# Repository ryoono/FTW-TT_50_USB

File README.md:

# FTW-TT_50_USB  

<span style="color: red; ">F</span>ake <span style="color: red; ">T</span>ype <span style="color: red; ">W</span>riter - <span style="color: red; ">T</span>etora <span style="color: red; ">T</span>ech lab _ <span style="color: red; ">5</span>.<span style="color: red; ">0</span>v _ <span style="color: red; ">USB</span> drive  
テトラ技研製 USB駆動 ニセタイプライター  

**[紹介動画](https://youtu.be/UQrdH8_pX44?si=VVSs2FK_6RHxstvM)**

## 背景  
現代の消音キーボードに反抗すべく、タイプライターを叩いた時の音を楽しめるデバイスを作成する。  
タイプライター風キーボードも売ってはいるが、それを使っては味気ないので、外付けUSBデバイスとして実装する。  
当初、リレーで音を出そうと考えていたが、よくよく調べてみると二番煎じだった。  
そのため、急遽ソレノイドで音を出す仕様に変更した...   
[Silriumさん_USB KeyBoard RELAY](https://makezine.jp/blog/2015/08/mft2015_silrium.html)

## 概要  
キータイプ時にソレノイドを動作させ、タイプライターの音を表現する。  
音は2種類用意する。

| キー種類     | 音           | 備考                   | 
| ------------ | ------------ | ---------------------- | 
| 一般キー     | メカニカル音 | エンターキー以外のキー | 
| エンターキー | ベル音       |                        |  

メカニカル音はソレノイドの動作音で再現する。  
ベル音はタイプライターの文字送り催促ベルを指しており、自転車のベルで再現する。  

## ハードウェア設計  
### 構成  
一般キー押下時の音を再現するために、ソレノイドを接続する。  
タイピングの間隔が80msを下回ると、ソレノイドのデッドタイムとかぶるため、一般キー用のソレノイドを2つ接続して対策する。  
エンターキー押下時の音は、ベルを鳴らすことで対応する。  
なお、エンターキーの押下間隔は80msを下回らないと仮定して、ソレノイドは1つのみ接続する。  

### 回路図  
小型化を狙いpicマイコンで実装しようとしたが、時間が無いのでArduinoを使用する。  
Arduino Microを使用して設計したが、電源回りが弱いようで5Vピンから5V出力されないため、Nanoを使用する。  
使用するソレノイドには、ON/OFF 40[ms]ずつ計80[ms]のデッドタイムがあり、一般キー押下タイミングによっては、反応が追い付かない。  
そのため、ソレノイドを2個設置し、40[ms]のデッドタイムとすることで対応する。  
なお、2個以上のソレノイドを同時に動作させることはUSB2.0の規格上、電流が大きすぎるため同時動作ソレノイドは1つまでとする。  

## ソフトウェア設計  
### PC側  
```mermaid
---
title: Fig. PC側処理_フローチャート
---

flowchart TD
    start1([開始])
    node0[Arduinoとの通信開始]
    node1[キーイベント監視開始]
    end1([終了])

    start2([キーイベント発生])
    node2[押下キー取得]
    switch1{押下キー}
    node3[Arduinoに'0'を送信]
    node4[Arduinoに'1'を送信]
    end2([終了])

    start1 --> node0
    node0 --> node1
    node1 --> end1

    start2 --> node2
    node2 --> switch1
    switch1 -- エンターキー --> node3
    switch1 -- エンターキー以外 --> node4
    node3 --> end2
    node4 --> end2
```

### デバイス側  
なぜ関数化しなかったのかが悔やまれるが、展示ギリギリだったので許してほしい。  

```mermaid
---
title: Fig. Arduino側処理_フローチャート
---

flowchart TD
    start1([開始])
    node0[シリアル受信チェック]
    switch0{受信有無}
    switch1{打鍵タイプ}
    switch2{受信キー}
    switch2_1{受信キー}
    node1[受信キーBuff = エンターキー]
    switch3{受信キーBuff}
    node2[受信キーBuff = 一般キー]
    node2_1[受信キーBuff = 一般キー]
    switch4{ソレノイド状態}
    end1([終了])

    start1 --> node0
    node0 --> switch0
    switch0 -- あり --> switch1
    switch1 -- 英語(1) --> switch2
    switch2 -- エンターキー('0') --> node1
    switch2 -- 一般キー('1') --> switch3
    switch3 -- なし(0) --> node2
    switch1 -- 日本語(0) --> switch2_1
    switch2_1 -- エンターキー('0') | 一般キー('1') --> node2_1
    node1 --> switch4
    node2 --> switch4
    switch2 -- それ以外--> switch4
    switch3 -- あり(!=0) --> switch4
    node2_1 --> switch4
    switch2_1 -- それ以外 --> switch4
    switch0 -- なし --> switch4

    switch10{受信キーBuff}
    node10[ソレノイドON時間設定 = 35ms]
    node11[ON中ソレノイドID = 3:エンターキー]
    node12[受信キーBuff初期化]

    node13[ソレノイドON時間設定 = 40ms]
    switch11{一般キーONソレノイド前回値}
    node14[ON中ソレノイドID = 1:一般キー]
    node14[ON中ソレノイドID = 2:一般キー]
    node15[受信キーBuff初期化]

    switch4 -- ON中(0以外) --> switch10
    switch10 -- エンターキー(1) --> node10
    node10 --> node11
    node11 --> node12
    switch10 -- 一般キー(0) --> node13
    node13 --> switch11
    switch11 -- 1 --> node14
    switch11 -- 2 --> node15

    switch20{ソレノイドON時間設定}
    switch21{ON中ソレノイドID}
    node20[ソレノイド1のみON]
    node21[ソレノイド2のみON]
    node22[ソレノイド3のみON]
    node23[ソレノイド全OFF]

    node30[1ms停止]

    node12 --> switch20
    node14 --> switch20
    node15 --> switch20
    switch20 -- 0以外 --> switch21
    switch21 -- 1:一般キー --> node20
    switch21 -- 2:一般キー --> node21
    switch21 -- 3:エンターキー --> node22
    switch20 -- 0 --> node23

    node20 --> node30
    node21 --> node30
    node22 --> node30
    node23 --> node30

    node30 --> end1
```

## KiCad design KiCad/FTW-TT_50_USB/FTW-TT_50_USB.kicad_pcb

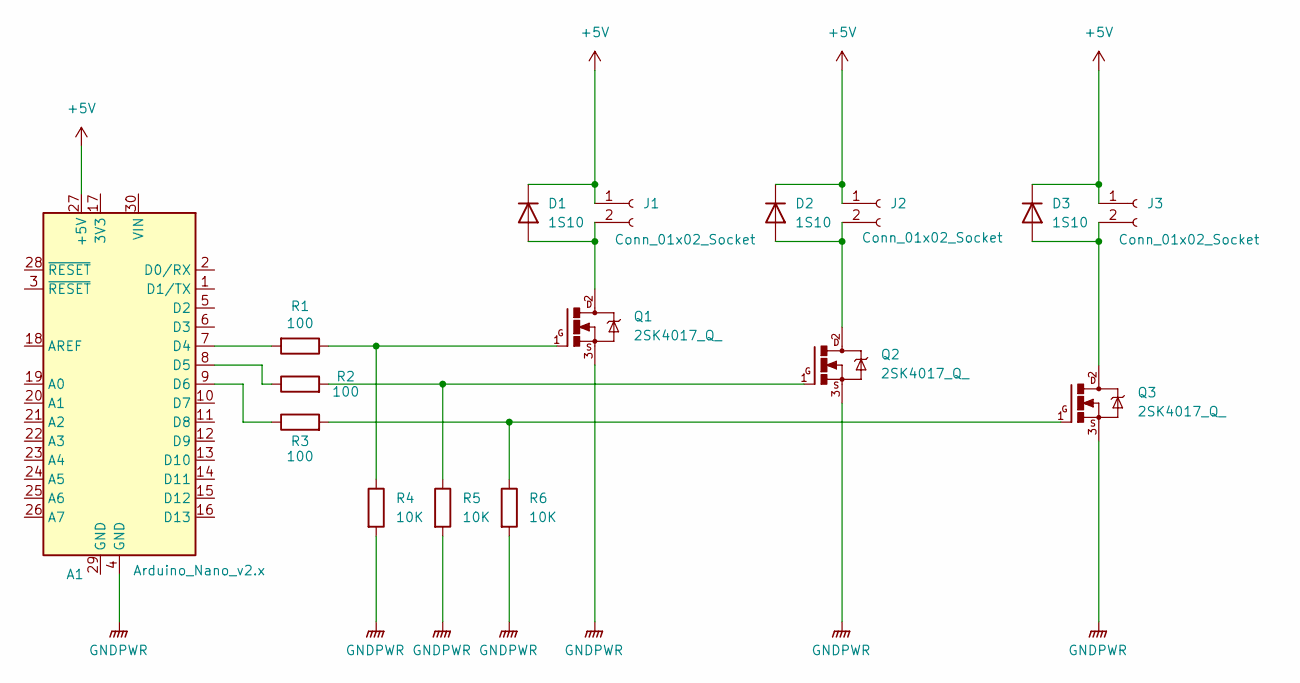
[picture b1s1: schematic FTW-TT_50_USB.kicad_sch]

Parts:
A1: Arduino_Nano_v2.x; Arduino_Nano
D1, D2, D3: 1S10; D_DO-41_SOD81_P7.62mm_Horizontal
J1, J2, J3: Conn_01x02_Socket; JST_XH_B2B-XH-AM_1x02_P2.50mm_Vertical
Q1, Q2, Q3: 2SK4017_Q_; TO230P230X650X740-3P
R1, R2, R3: 100; R_Axial_DIN0207_L6.3mm_D2.5mm_P10.16mm_Horizontal
R4, R5, R6: 10K; R_Axial_DIN0207_L6.3mm_D2.5mm_P10.16mm_Horizontal

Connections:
+5V: A1.27 (+5V), D1.1 (K), D2.1 (K), D3.1 (K), J1.1, J2.1, J3.1
GNDPWR: A1.4 (GND), Q1.3, Q2.3, Q3.3, R4.2, R5.2, R6.2
unnamed: A1.7 (D4), R1.2
unnamed: A1.8 (D5), R2.1
unnamed: A1.9 (D6), R3.1
unnamed: D1.2 (A), J1.2, Q1.2
unnamed: D2.2 (A), J2.2, Q2.2
unnamed: D3.2 (A), J3.2, Q3.2
unnamed: Q1.1, R1.1, R4.1
unnamed: Q2.1, R2.2, R5.1
unnamed: Q3.1, R3.2, R6.1

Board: 2 copper layers, 16 parts (0 on the bottom side), 11 nets, no tracks yet.

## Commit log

2023-03-30 パーツリスト更新
2023-04-02 Delete ~$電子部品.xlsx
    一時ファイル削除
2023-04-03 回路図追加
2023-04-04 雛形作成
2023-04-05 概要追記
2023-04-06 回路図追記
2023-04-07 模索用ディレクトリ追加
2023-04-07 メモを追加
2023-04-07 ソレノイド動作チェックS/W雛形追加
2023-04-08 模索の取説書き始め
2023-04-09 取説追加
2023-04-09 コマンド受け取る処理実装
2023-04-09 ソレノイド稼働処理実装
2023-04-11 結果記載
2023-04-12 動かなかった箇所の修正
2023-04-13 少し追記(特に変更無し)
2023-04-16 名称追加
2023-10-07 回路図反映
2023-10-07 背景追記
2023-10-15 デバイス側プロジェクトファイル作成
2023-10-15 既存のサンプルコード使うことにした
2023-10-15 サンプルコード_コンパイル確認
2023-10-15 出典記載、メモ追加
2023-10-15 文字コードをutf-8に変更
2023-10-23 バックグラウンドキー取得模索格納
2023-10-23 コメント追加
2023-10-23 バックグラウンドキー取得&Arduinoと通信するコード追加(動作未確認)
2023-10-24 動作確認済み(エンター以外)
2023-10-24 メモ追加
2023-10-24 設計変更反映(デバイス側ICの変更)
2023-10-25 通信速度修正 & ソレノイド2個に対応改修
2023-10-26 エンターキー押下時の不具合修正
2023-10-28 ベル動作確認用土台追加
2023-10-31 固定台追加
2023-10-31 コード調整
2023-11-01 EN/JPモード追加
2023-11-01 プレート追加
2023-11-01 picのプロジェクトフォルダを削除
2023-11-18 NT名古屋最終
2024-01-14 誤記修正
2024-07-07 紹介動画の追加 & 句読点の統一(，→、)
2024-07-07 PC側処理のフローチャート追加
2024-07-07 PC側ふとーチャート画像追加
2024-07-07 不必要な処理削除 & コメント修正
2024-07-07 Arduino側フローチャート追加
2024-07-07 画像サイズ修正
2024-07-07 ハードウェア構成追加
2024-07-07 外観画像追加
2025-06-17 KiCadファイル追加
